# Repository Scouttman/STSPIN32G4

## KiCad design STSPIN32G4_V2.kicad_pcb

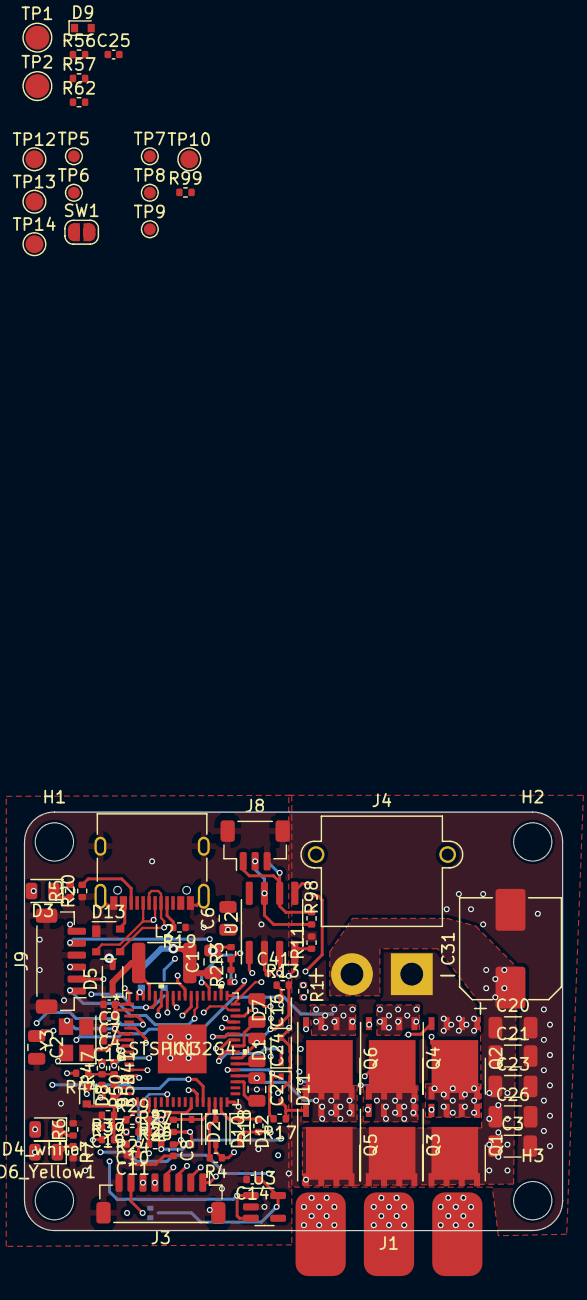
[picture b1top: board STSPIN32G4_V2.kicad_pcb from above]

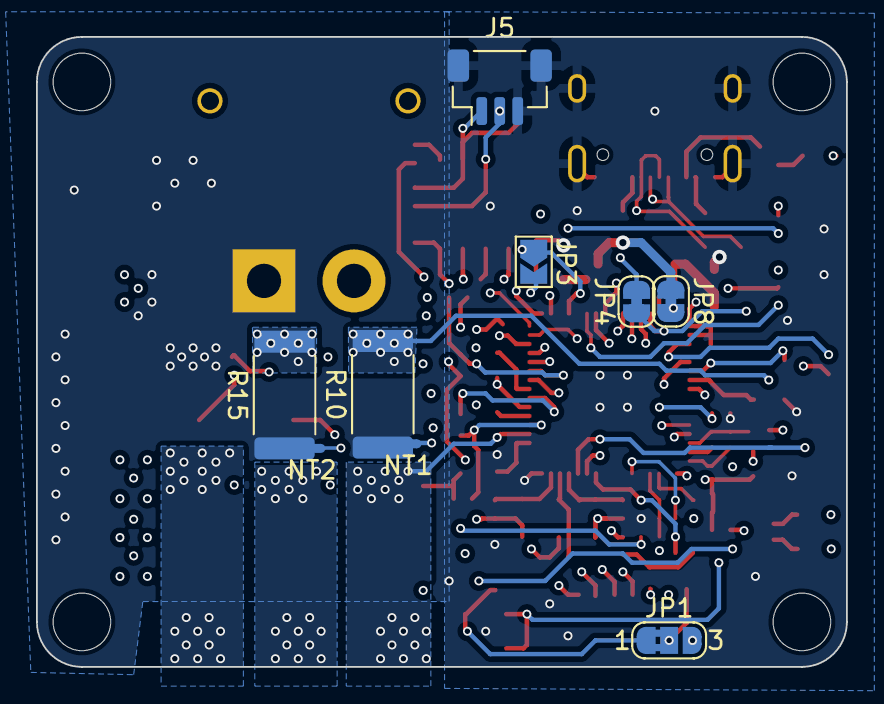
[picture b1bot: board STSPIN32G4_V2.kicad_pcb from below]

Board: 4 copper layers, 45.0 x 35.0 mm, 109 parts (9 on the bottom side), 73 nets.

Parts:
C1: 10uf 25v; C_0805_2012Metric
C2: 220nF; C_0805_2012Metric
C3, C20, C21, C23, C26: 2.2uf; C_1206_3216Metric
C4, C18: 20p; C_0402_1005Metric
C6: 10uF; C_0805_2012Metric
C7, C9, C11, C41: 100nF; C_0402_1005Metric
C8, C10, C14: 1uF; C_0402_1005Metric
C16, C24, C27: 1uF; C_0805_2012Metric
C19: 33nf; C_0402_1005Metric
C25: 82nF; C_0402_1005Metric
C31: 220uF; CP_Elec_8x10
D1, D2, D7, D10, D11, D12: 1N4148WS; D_SOD-323
D3, D4_white1, D6_Yellow1: LED; LED_0805_2012Metric
D5: SS210; D_SOD-323
D8: BAT30k; D_SOD-523
D9: D_Schottky; D_SOD-523
D13: PRTR5V0U2X; SOT-143
H1, H2, H3, H4: MountingHole; MountingHole_3.2mm_M3_ISO14580
IC1: STSPIN32G4
J1: Conn_01x03_Pin; flat_3
J3: Conn_01x08_MountingPin; JST_SH_BM08B-SRSS-TB_1x08-1MP_P1.00mm_Vertical
J4: Conn_01x02_Female; AMASS_XT30PW-M_1x02_P2.50mm_Horizontal
J5, J8: Conn_01x03_MountingPin; JST_SH_BM03B-SRSS-TB_1x03-1MP_P1.00mm_Vertical
J9: Conn_01x06_MountingPin; JST_SH_BM06B-SRSS-TB_1x06-1MP_P1.00mm_Vertical
J14: USB_C_Receptacle_USB2.0; USB_C_Receptacle_XKB_U262-16XN-4BVC11
JP1: Jumper_3_Bridged12; SolderJumper-3_P1.3mm_Bridged2Bar12_RoundedPad1.0x1.5mm_Num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
JP3: Jumper_2_Open; SolderJumper-2_P1.3mm_Open_TrianglePad1.0x1.5mm
JP4, JP8: Jumper_2_Bridged; SolderJumper-2_P1.3mm_Bridged_RoundedPad1.0x1.5mm
L2: 18uh; L_1812_4532Metric
NT1, NT2: NetTie_2; NetTie-2_SMD_Pad0.5mm
Q1, Q2, Q3, Q4, Q5, Q6: Q_NMOS_GDS; DFN-8-1EP_6x5mm_P1.27mm_EP4x4mm
R1, R4, R13, R17, R18, R25: 33; R_0402_1005Metric
R2, R3, R11: 10k; R_0402_1005Metric
R5, R6: 220; R_0402_1005Metric
R7: 110; R_0402_1005Metric
R10, R15: 4mΩ; R_2512_6332Metric
R19, R20: 5.1k; R_0402_1005Metric
R23, R24, R44, R50: 1.5k; R_0402_1005Metric
R26, R27, R41, R47: 22k; R_0402_1005Metric
R29, R53: 11k; R_0402_1005Metric
R37: 72.3k; R_0402_1005Metric
R39: 3.01k; R_0402_1005Metric
R56: 68k; R_0402_1005Metric
R57: 27k; R_0402_1005Metric
R62: 3.9k; R_0402_1005Metric
R98: 120; R_0402_1005Metric
R99: 10K; R_0402_1005Metric
SW1: SW_Push; SolderJumper-2_P1.3mm_Open_RoundedPad1.0x1.5mm
TP1, TP2: TestPoint; TestPoint_Pad_D2.0mm
TP5, TP6, TP7, TP8, TP9: TestPoint; TestPoint_Pad_D1.0mm
TP10, TP12, TP13, TP14: TestPoint; TestPoint_Pad_D1.5mm
U2: TJA1057T/1Z; SOIC-8_3.9x4.9mm_P1.27mm
U3: TC1017-xCT; SOT-23-5
Y3: 24mhz; Crystal_SMD_3225-4Pin_3.2x2.5mm

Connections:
+5V: C14.1, JP1.1 (A), U3.5 (VOUT)
/Inputs_out_Puts/VBUS: D13.4 (VCC), J14.A4 (VBUS), J14.A9 (VBUS), J14.B4 (VBUS), J14.B9 (VBUS)
BOOT1: C16.2, IC1.41 (BOOT1)
BOOT2: C24.2, IC1.38 (BOOT2)
BOOT3: C27.2, IC1.35 (BOOT3)
CAN_SHDN: IC1.58 (PB7), R99.1
D+: D13.2 (I/O1), IC1.48 (PA12), J14.A6 (D+), J14.B6 (D+)
D-: D13.3 (I/O2), IC1.47 (PA11), J14.A7 (D-), J14.B7 (D-)
DAC2: IC1.18 (PA5), TP14.1
FDCAN1_RX/BOOT_0: IC1.59 (PB8), R11.1, SW1.1, U2.4 (RXD)
FDCAN1_TX: IC1.60 (PB9), U2.1 (TXD)
GHS1: D7.1 (K), IC1.43 (GHS1), R13.2
GHS2: D1.1 (K), IC1.40 (GHS2), R1.2
GHS3: D11.1 (K), IC1.37 (GHS3), R17.2
GLS1: D2.1 (K), IC1.29 (GLS1), R25.2
GLS2: D10.1 (K), IC1.30 (GLS2), R4.2
GLS3: D12.1 (K), IC1.31 (GLS3), R18.2
GND: C1.2, C2.2, C3.2, C4.2, C6.2, C7.2, C8.2, C9.2, C10.2, C11.2, C14.2, C18.2, C19.2, C20.2, C21.2, C23.2, C25.2, C26.2, C31.2, C41.1, D5.2 (A), D13.1 (GND), IC1.32 (PGND), IC1.65 (VSS), J3.8, J3.MP (MountPin), J4.1, J5.3, J5.MP (MountPin), J8.3, J8.MP (MountPin), J9.4, J9.MP (MountPin), J14.A1 (GND), J14.A12 (GND), J14.B1 (GND), J14.B12 (GND), J14.S1 (SHIELD), NT1.2, NT2.2, Q2.3 (S), R3.2, R5.2, R6.2, R7.2, R10.1, R11.2, R15.1, R19.1, R20.1, R27.2, R39.2, R47.2, R62.2, U2.2 (GND), U3.2 (GND), Y3.2, Y3.4
GPIO_PA10: IC1.46 (PA10), J3.1
I2C2_SCL: IC1.45 (PA9), J3.3
I2C2_SDA: IC1.44 (PA8), J3.2
unnamed: D1.2 (A), Q3.1 (G), R1.1
unnamed: D2.2 (A), Q2.1 (G), R25.1
unnamed: D3.1 (K), R5.1
unnamed: D4_white1.1 (K), R6.1
unnamed: D6_Yellow1.1 (K), R7.1
unnamed: D7.2 (A), Q1.1 (G), R13.1
unnamed: D10.2 (A), Q4.1 (G), R4.1
unnamed: D11.2 (A), Q5.1 (G), R17.1
unnamed: D12.2 (A), Q6.1 (G), R18.1
unnamed: IC1.51 (PA15), TP12.1
unnamed: IC1.53 (PD2), TP13.1
unnamed: C2.1, IC1.61 (VM), JP4.1 (A)
unnamed: J3.7, JP1.2 (C)
unnamed: J5.1, J8.1, R98.2, U2.6 (CANL)
unnamed: J5.2, J8.2, R98.1, U2.7 (CANH)
unnamed: J14.A5 (CC1), R19.2
unnamed: J14.B5 (CC2), R20.2
unnamed: C1.1, JP8.1 (A), L2.2
unnamed: R56.1, R57.2
unnamed: R99.2, U2.8 (S)
OPN1: IC1.16 (PA3), R50.1, R53.2
OPN2: IC1.22 (PC5), R24.1, R29.2
OPO1: IC1.15 (PA2), R53.1, TP2.1
OPO2: IC1.19 (PA6), R29.1
OPP1: IC1.14 (PA1), R41.2, R44.1, R47.1, TP1.1
OPP2: IC1.20 (PA7), R23.1, R26.2, R27.1
OSC_IN: C4.1, IC1.6 (PF0), Y3.3
OSC_OUT: C18.1, IC1.7 (PF1), Y3.1
OUT1: C16.1, IC1.42 (OUT1), J1.3, Q1.3 (S), Q2.2 (D), R56.2
OUT2: C24.1, IC1.39 (OUT2), J1.2, Q3.3 (S), Q4.2 (D)
OUT3: C27.1, IC1.36 (OUT3), J1.1, Q5.3 (S), Q6.2 (D)
PC0: C25.1, D9.2 (A), R57.1, R62.1
SCREF: IC1.52 (SCREF), JP3.1 (A), R2.2, R3.1
SPI1_MISO: IC1.55 (PB4), J3.5
SPI1_MOSI: IC1.56 (PB5), J3.4
SPI1_NSS: IC1.17 (PA4), TP10.1
SPI1_SCK: IC1.54 (PB3), J3.6, J9.1
SW: D5.1 (K), IC1.62 (SW), L2.1
SWCLK: IC1.50 (PA14), J9.5
SWDIO: IC1.49 (PA13), J9.3
USER1: D4_white1.2 (A), IC1.3 (PC13)
USER2: D6_Yellow1.2 (A), IC1.28 (PB10)
VBUS_Monitor: C19.1, D8.2 (A), IC1.13 (PA0), R37.2, R39.1
VCC: IC1.63 (VCC), IC1.64 (REGIN), JP8.2 (B), TP6.1, U3.1 (VIN), U3.3 (~SHDN)
VDD: C6.1, C7.1, C8.1, C9.1, C41.2, D3.2 (A), D8.1 (K), D9.1 (K), IC1.1 (REG3V3/VDD), IC1.2 (VBAT), IC1.27 (VDDA), J9.6, JP1.3 (B), JP3.2 (B), R2.1, SW1.2, TP5.1, U2.3 (VCC)
VM: C3.1, C20.1, C21.1, C23.1, C26.1, C31.1, J4.2, JP4.2 (B), Q1.2 (D), Q3.2 (D), Q5.2 (D), R37.1
VREF+: C10.1, C11.1, IC1.26 (VREF+), R26.1, R41.1
VSHUNT1N: NT1.1, R50.2
VSHUNT1P: Q6.3 (S), R10.2, R44.2
VSHUNT2N: NT2.1, R24.2
VSHUNT2P: Q4.3 (S), R15.2, R23.2
nRST: IC1.8 (PG10), J9.2

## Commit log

2023-10-10 revision 4
2023-10-10 jlcpcb production files
2023-10-23 uploaded missing schematics

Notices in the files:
parts and their libraries:
Copyright 2021 Accelerated Designs. All rights reserved.
